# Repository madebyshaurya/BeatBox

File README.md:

# BeatBox
## Control your spotify music with style!
Think of it as Alexa but it shows your current playing music on the screen and you can use voice commands to change it or play a new song!

## Visuals

### Schematic

### PCB

### BOM

| Designator    | Footprint                                                | Quantity | Value         |
|--------------|-----------------------------------------------------------|----------|---------------|
| BT1          | BatteryHolder_Keystone_1042_1x18650                       | 1        | Battery_Cell  |
| C1           | CP_Radial_D10.0mm_P5.00mm                                 | 1        | 1000µF        |
| C2, C3       | C_Disc_D5.0mm_W2.5mm_P5.00mm                              | 2        | 0.1µF         |
| C4, C5       | C_Disc_D5.0mm_W2.5mm_P5.00mm                              | 2        | 4.7µF         |
| C6, C7       | C_Disc_D5.0mm_W2.5mm_P5.00mm                              | 2        | 10µF          |
| C8           | C_Disc_D5.0mm_W2.5mm_P5.00mm                              | 1        | 100µF         |
| C9           | C_Disc_D5.0mm_W2.5mm_P5.00mm                              | 1        | 0.1uF         |
| D1           | LED_WS2812B_PLCC4_5.0x5.0mm_P3.2mm                        | 1        | WS2812B       |
| M2           | Mic_INMP441_Custom                                       | 1        | ~             |
| R1           | R_Axial_DIN0207_L6.3mm_D2.5mm_P7.62mm_Horizontal          | 1        | 330           |
| R2, R3       | R_Axial_DIN0207_L6.3mm_D2.5mm_P7.62mm_Horizontal          | 2        | 10kΩ          |
| R4           | R_Axial_DIN0207_L6.3mm_D2.5mm_P7.62mm_Horizontal          | 1        | 100k          |
| R5           | R_Axial_DIN0207_L6.3mm_D2.5mm_P7.62mm_Horizontal          | 1        | 27k           |
| SW1          | SW_DIP_SPSTx01_Slide_6.7x4.1mm_W7.62mm_P2.54mm_LowProfile | 1        | SW_SPST       |
| U1           | ILI9341                                                  | 1        | TFT_320x240   |
| U2           | SOT229P700X180-4N                                        | 1        | AMS1117-3.3   |
| U3           | ESP32-S3-DevKitC                                         | 1        | ESP32-S3-DevKitC |
| U4           | TP4056                                                   | 1        | TP4056_Module |

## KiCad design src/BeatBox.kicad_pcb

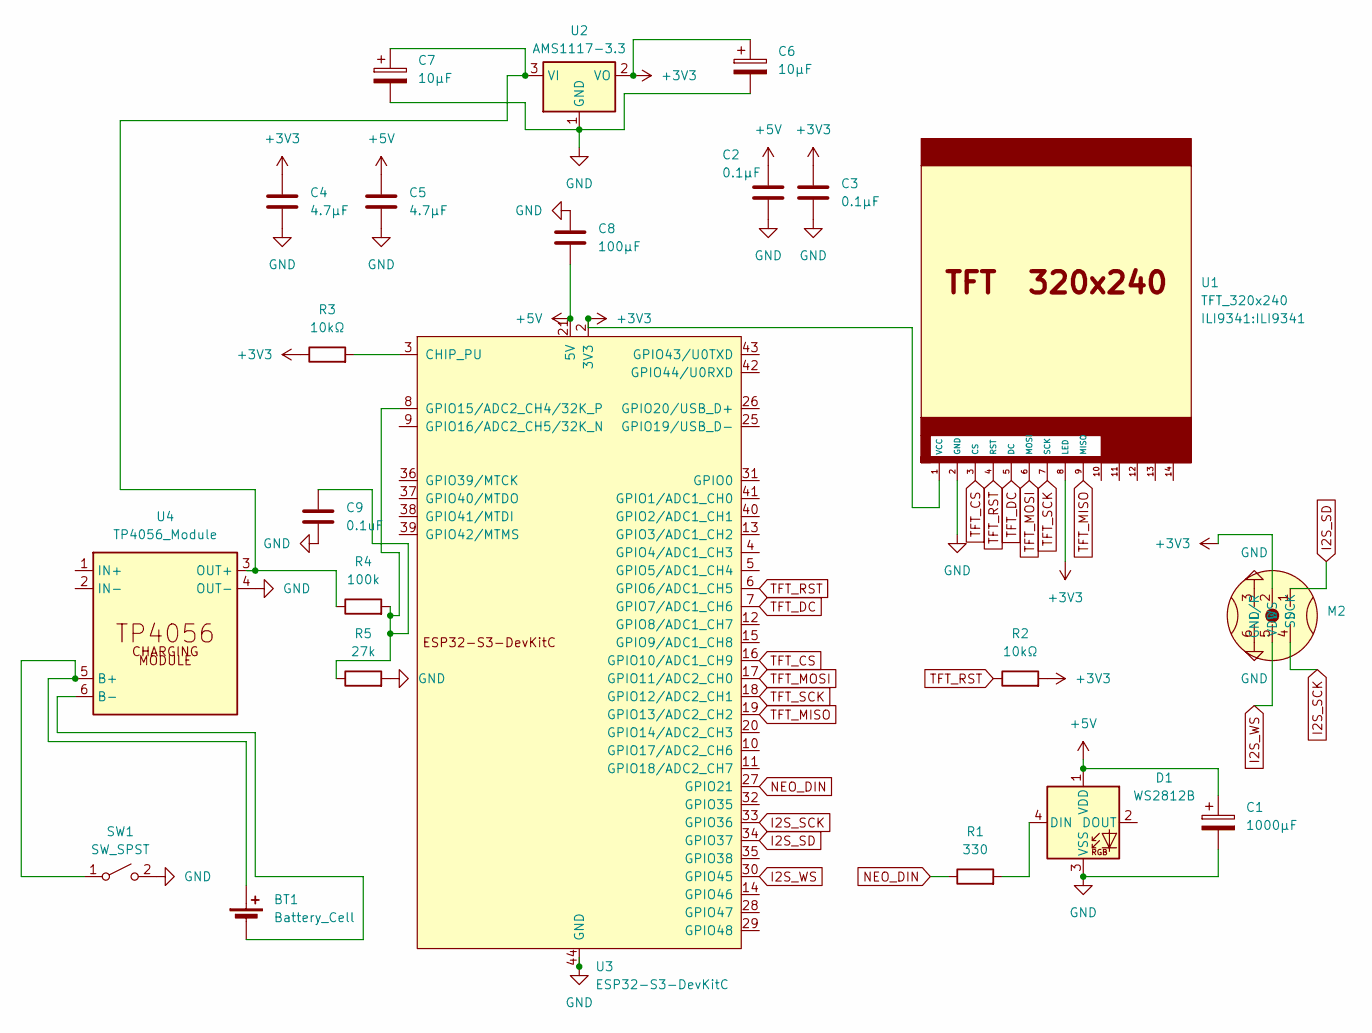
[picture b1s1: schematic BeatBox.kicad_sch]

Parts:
BT1: Battery_Cell; BatteryHolder_Keystone_1042_1x18650
C1: 1000µF; CP_Radial_D10.0mm_P5.00mm
C2, C3: 0.1µF; C_Disc_D5.0mm_W2.5mm_P5.00mm
C4, C5: 4.7µF; C_Disc_D5.0mm_W2.5mm_P5.00mm
C6, C7: 10µF; C_Disc_D5.0mm_W2.5mm_P5.00mm
C8: 100µF; C_Disc_D5.0mm_W2.5mm_P5.00mm
C9: 0.1uF; C_Disc_D5.0mm_W2.5mm_P5.00mm
D1: WS2812B; LED_WS2812B_PLCC4_5.0x5.0mm_P3.2mm
M2: Mic_INMP441_Custom
R1: 330; R_Axial_DIN0207_L6.3mm_D2.5mm_P7.62mm_Horizontal
R2, R3: 10kΩ; R_Axial_DIN0207_L6.3mm_D2.5mm_P7.62mm_Horizontal
R4: 100k; R_Axial_DIN0207_L6.3mm_D2.5mm_P7.62mm_Horizontal
R5: 27k; R_Axial_DIN0207_L6.3mm_D2.5mm_P7.62mm_Horizontal
SW1: SW_SPST; SW_DIP_SPSTx01_Slide_6.7x4.1mm_W7.62mm_P2.54mm_LowProfile
U1: TFT_320x240; ILI9341
U2: AMS1117-3.3; SOT229P700X180-4N
U3: ESP32-S3-DevKitC
U4: TP4056_Module; TP4056

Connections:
+3V3: C3.1, C4.1, C6.1, M2.2 (VDD), R2.2, R3.1, U1.1 (VCC), U1.8 (LED), U2.2 (VO), U3.1 (3V3), U3.2 (3V3)
+5V: C1.1, C2.1, C5.1, C8.2, D1.1 (VDD), U3.21 (5V)
GND: C1.2, C2.2, C3.2, C4.2, C5.2, C6.2, C7.2, C8.1, C9.2, D1.3 (VSS), M2.3 (GND), M2.6 (L/R), R5.2, SW1.2 (B), U1.2 (GND), U2.1 (GND), U3.22 (GND), U3.23 (GND), U3.24 (GND), U3.44 (GND), U4.4 (OUT-)
I2S_SCK: M2.4 (SCK), U3.33 (GPIO36)
I2S_SD: M2.1 (SD), U3.34 (GPIO37)
I2S_WS: M2.5 (WS), U3.30 (GPIO45)
NEO_DIN: R1.1, U3.27 (GPIO21)
unnamed: BT1.1 (+), SW1.1 (A), U4.5 (B+)
unnamed: BT1.2 (-), U4.6 (B-)
unnamed: D1.4 (DIN), R1.2
unnamed: C7.1, R4.1, U2.3 (VI), U4.3 (OUT+)
unnamed: R3.2, U3.3 (CHIP_PU)
unnamed: C9.1, R4.2, R5.1, U3.8 (GPIO15/ADC2_CH4/32K_P)
TFT_CS: U1.3 (CS), U3.16 (GPIO10/ADC1_CH9)
TFT_DC: U1.5 (DC), U3.7 (GPIO7/ADC1_CH6)
TFT_MISO: U1.9 (MISO), U3.19 (GPIO13/ADC2_CH2)
TFT_MOSI: U1.6 (MOSI), U3.17 (GPIO11/ADC2_CH0)
TFT_RST: R2.1, U1.4 (RST), U3.6 (GPIO6/ADC1_CH5)
TFT_SCK: U1.7 (SCK), U3.18 (GPIO12/ADC2_CH1)

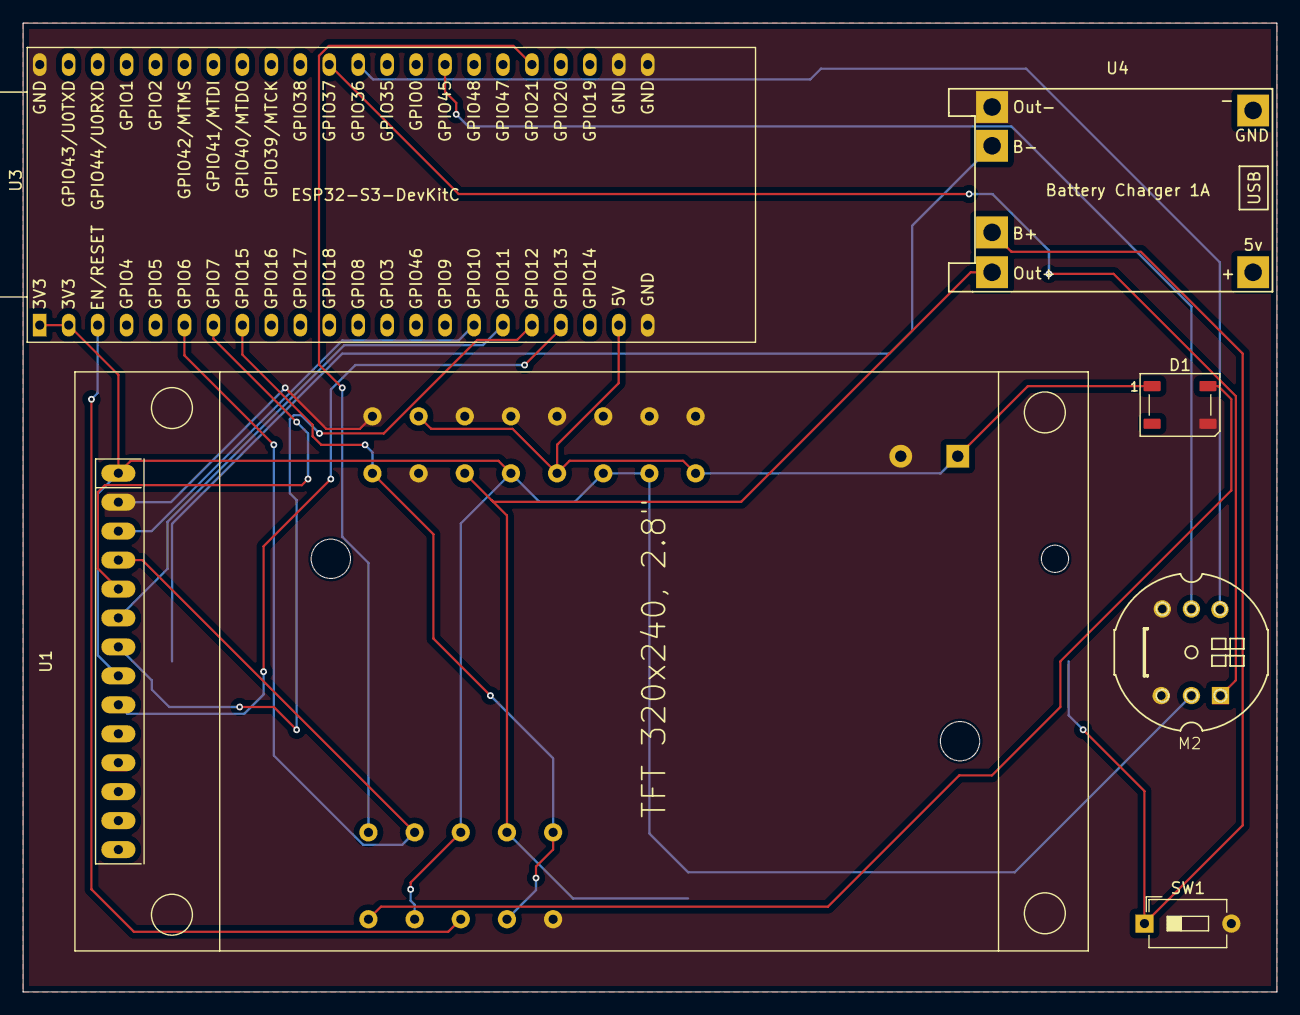
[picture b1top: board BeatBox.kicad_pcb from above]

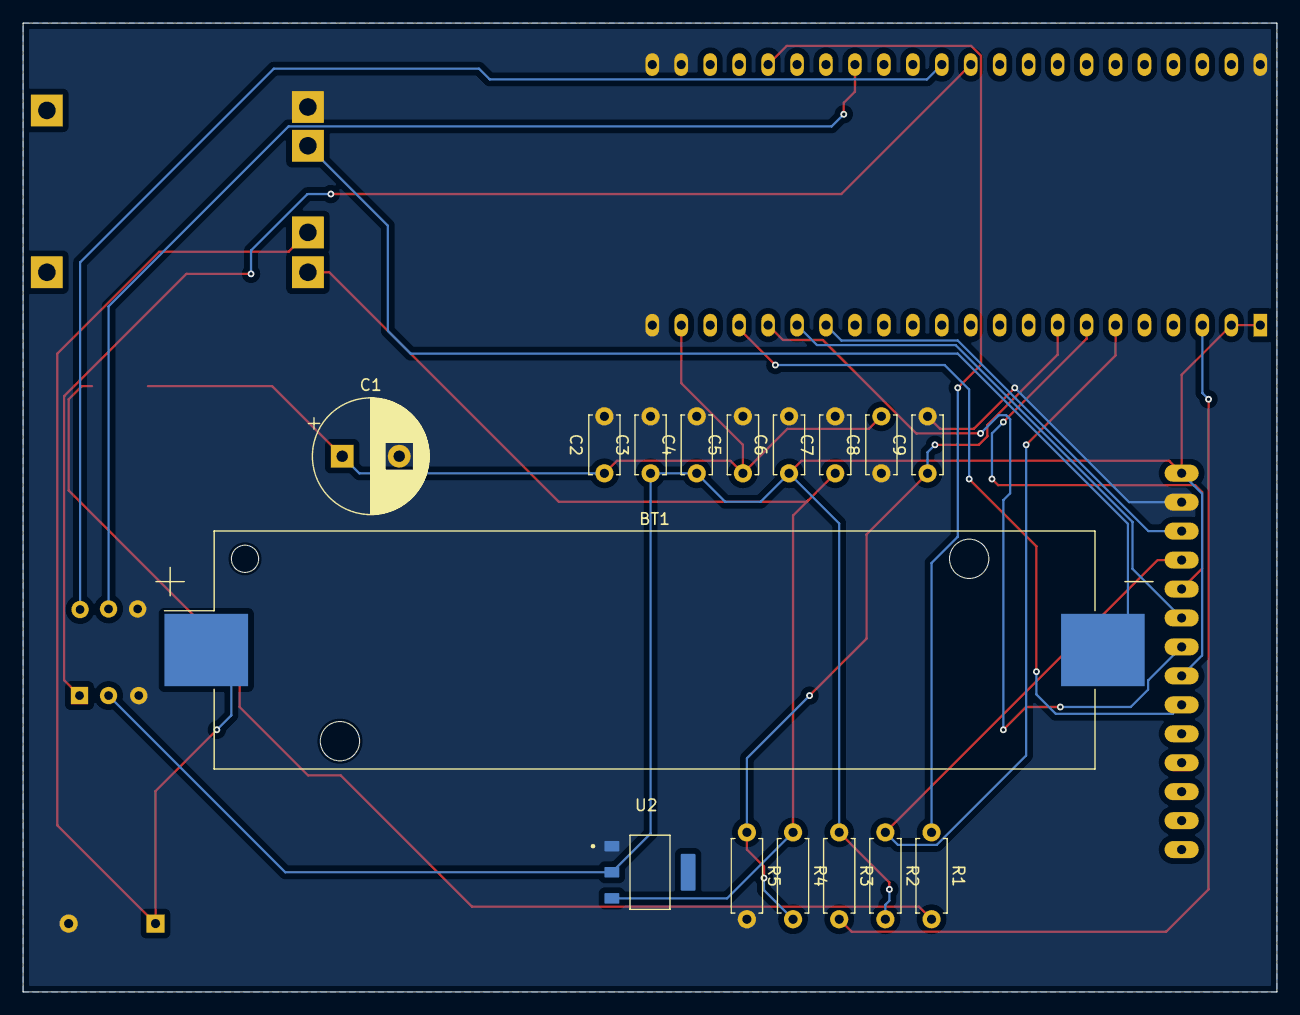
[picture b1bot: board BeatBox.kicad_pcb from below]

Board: 2 copper layers, 110.0 x 85.0 mm, 22 parts (16 on the bottom side), 19 nets.

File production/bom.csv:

Designator,Footprint,Quantity,Value,LCSC Part #
BT1,BatteryHolder_Keystone_1042_1x18650,1,Battery_Cell,
C1,CP_Radial_D10.0mm_P5.00mm,1,1000µF,
"C2, C3",C_Disc_D5.0mm_W2.5mm_P5.00mm,2,0.1µF,
"C4, C5",C_Disc_D5.0mm_W2.5mm_P5.00mm,2,4.7µF,
"C6, C7",C_Disc_D5.0mm_W2.5mm_P5.00mm,2,10µF,
C8,C_Disc_D5.0mm_W2.5mm_P5.00mm,1,100µF,
C9,C_Disc_D5.0mm_W2.5mm_P5.00mm,1,0.1uF,
D1,LED_WS2812B_PLCC4_5.0x5.0mm_P3.2mm,1,WS2812B,
M2,Mic_INMP441_Custom,1,~,
R1,R_Axial_DIN0207_L6.3mm_D2.5mm_P7.62mm_Horizontal,1,330,
"R2, R3",R_Axial_DIN0207_L6.3mm_D2.5mm_P7.62mm_Horizontal,2,10kΩ,
R4,R_Axial_DIN0207_L6.3mm_D2.5mm_P7.62mm_Horizontal,1,100k,
R5,R_Axial_DIN0207_L6.3mm_D2.5mm_P7.62mm_Horizontal,1,27k,
SW1,SW_DIP_SPSTx01_Slide_6.7x4.1mm_W7.62mm_P2.54mm_LowProfile,1,SW_SPST,
U1,ILI9341,1,TFT_320x240,
U2,SOT229P700X180-4N,1,AMS1117-3.3,
U3,ESP32-S3-DevKitC,1,ESP32-S3-DevKitC,
U4,TP4056,1,TP4056_Module,

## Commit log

2025-08-05 added pcb
2025-08-05 formatted as per guidelines
